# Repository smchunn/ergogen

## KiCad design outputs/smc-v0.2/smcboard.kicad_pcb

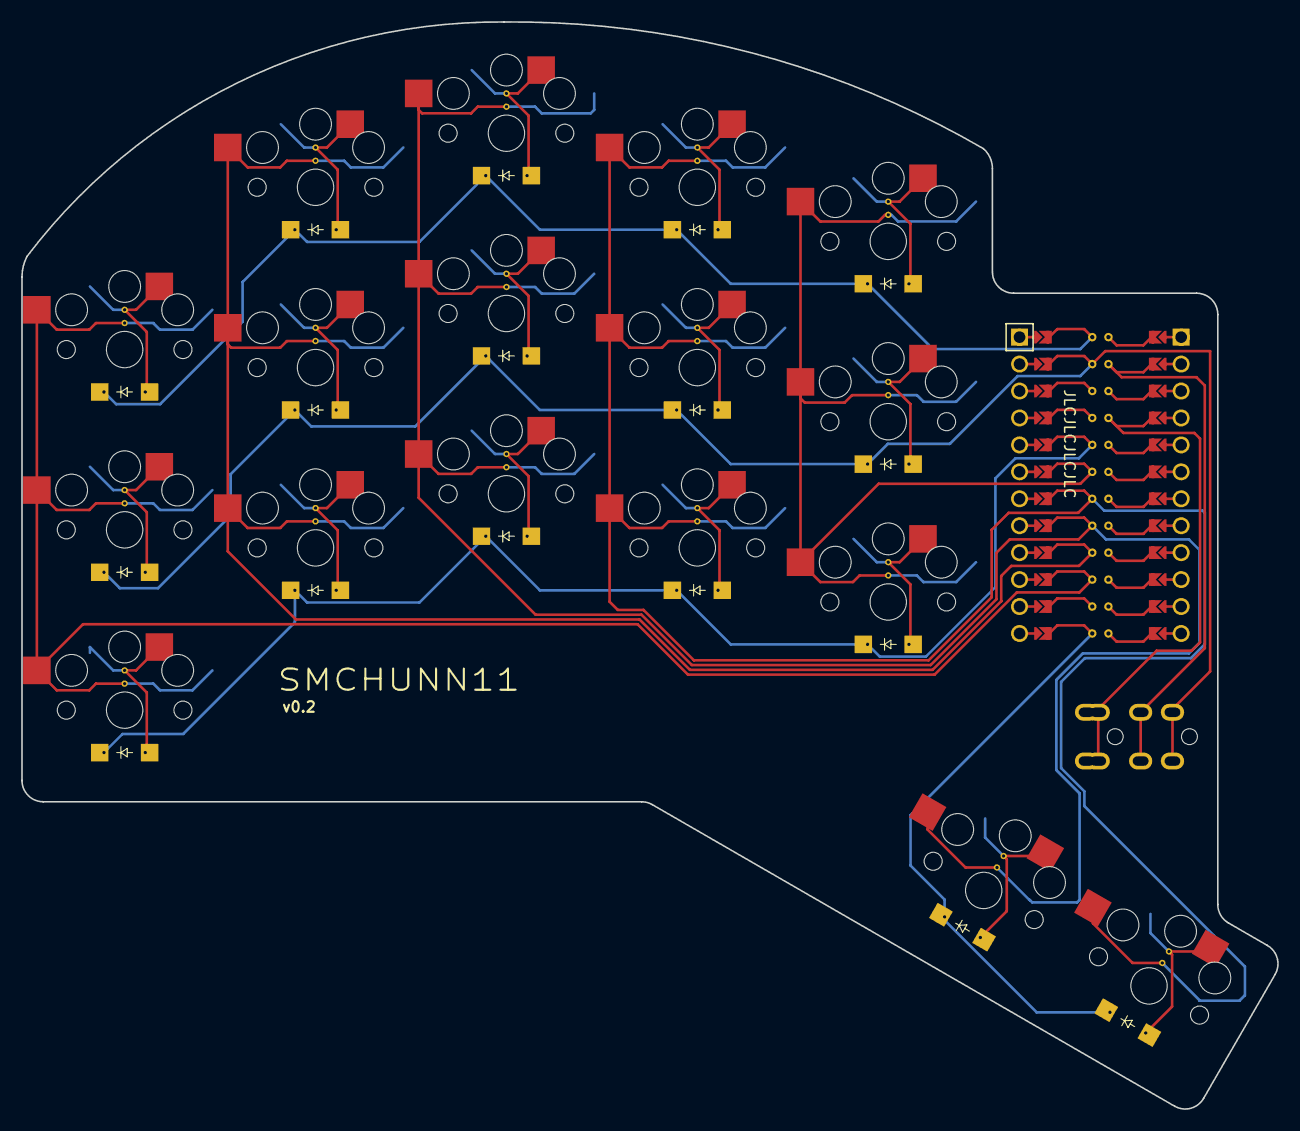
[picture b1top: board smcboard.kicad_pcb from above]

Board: 2 copper layers, 118.4 x 102.5 mm, 35 parts (0 on the bottom side), 27 nets.

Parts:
D1, D2, D3, D4, D5, D6, D7, D8, D9, D10, D11, D12, D13, D14, D15, D16, D17: ComboDiode
MCU1: ProMicro
S1, S2, S3, S4, S5, S6, S7, S8, S9, S10, S11, S12, S13, S14, S15, S16, S17: PG1350

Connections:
GND: MCU1.2, MCU1.21, MCU1.22
P0: D2.1, D5.1, D8.1, D11.1, D14.1, MCU1.23
P1: D3.1, D6.1, D9.1, D12.1, D15.1, MCU1.24
P2: D1.1, D4.1, D7.1, D10.1, D13.1, MCU1.20
P3: MCU1.19, S13.2, S14.2, S15.2
P4: MCU1.18, S10.2, S11.2, S12.2, S17.2
P5: MCU1.17, S7.2, S8.2, S9.2, S16.2
P6: MCU1.16, S4.2, S5.2, S6.2
P7: MCU1.15, S1.2, S2.2, S3.2
P9: D16.1, D17.1, MCU1.13
home_thumb: D17.2, S17.1
index_bottom: D10.2, S10.1
index_home: D11.2, S11.1
index_top: D12.2, S12.1
inner_bottom: D13.2, S13.1
inner_home: D14.2, S14.1
inner_top: D15.2, S15.1
middle_bottom: D7.2, S7.1
middle_home: D8.2, S8.1
middle_top: D9.2, S9.1
near_thumb: D16.2, S16.1
pinky_bottom: D1.2, S1.1
pinky_home: D2.2, S2.1
pinky_top: D3.2, S3.1
ring_bottom: D4.2, S4.1
ring_home: D5.2, S5.1
ring_top: D6.2, S6.1
